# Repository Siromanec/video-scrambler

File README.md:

# video-scrambler
This repository is for "Development of a Composite Baseband Video Signal (CVBS) scrambler" thesis.

## Description

This project contains:
 - Verilog HDL implementation (Quartus Prime 23.1std project) 
 - simulation setup (Modelsim Starter Edition 2021.1 project)
 - jupyter notebooks for visualization and validation of the algorithms
 - KiCAD 9.0 PCB designs for ADV7393 video encoder and TVP5147M1 video decoder

The Verilog implementation is based around line rotation algorithm for scrambling, 
Hash DRBG and SHA256 for number generation. 
It works with BT656 and SMPTE293M digital signal. 
Can synchronise the PRNGs even when the signal is lost. 
The scrambling pattern is different for each frame.
The number of frames before the pattern repeats is 2^32.
The delay is ~ 10^-8 s

The PCB design has the following features:
 - supplied with \> 5V
 - has 4 layers
 - separated power plains
 - all chips pins were wired to external pins (except chroma pins)
 - equalized paths

## Structure and  use
To open each project you need the corresponding IDE
### Notebooks
#### 1. `notebooks/config_creation`

It contains scripts for generating 256-bit seeds and putting them into `.mif` files for configuring the scrambler.

Generates complementary config files for the scrambler and descramber,
#### 2. `notebooks/functional_validation`
It was used to rewrite high-level python implementation
into verilog-friendly algorithm
#### 3. `notebooks/mp_to_bt656`

It contains a notebook used for converting `.mp4` video to `.bin` file compliant with bt656.

Additionally, it is used for visualization the scrambled and descrambled videos and contains the entropy calculations

Also, it has two videos: `aperol.mp4` and `church.mp4`. 
For simulation the user must convert the videos to
`aperol_f84.bin` and `church_f218.bin` and put them into

`FPGA/core/simulation/modelsim/data` or `FPGA/core/simulation/questa/data`

#### 4. `notebooks/randomness_validation`
It was used to validate that the generated random numbers are random
#### 5. `notebooks/resource_usage`
It was used to produce plots of resource usage as compiled by Quartus

### Verilog HDL implementation

`scrambler_mm` is the top module

`FPGA/core` contains the quartus project

`FPGA/core/src` contains rtl and tb code

`FPGA/core/include` contains rtl written by other developers

### Simulation setup

`FPGA/core/simulation/modelsim` contains the modelsim project

To provide the data for the simulation 
you must put it into `FPGA/core/simulation/modelsim/data`.
currently the simulations accepts only two types of files: files generated from `aperol_f84.bin` or `church_f218.bin`.
if you want to change it, you must modify the testbench with names of your files.
Once they are in there, open the project with `modelsim`, goto `project`, see a `sim` folder and in there run
`de/scrambler_mm_sim`. Run the scrambler first, and then the descrambler.
The results will be in `FPGA/core/simulation/modelsim/data` folder.

`FPGA/core/simulation/questa` is generated by quartus for RTL and Gate Level simulations. 
It was only used for GLS of scrambler_mm, because quartus has a bad interface for simulation, 
when the top module changes frequently.

When doing the GLS the user MUST CHANGE THE MIF FILE (for the corresponding functionality) 
AND UPDATE THE MIF FILE (in quartus) OR RECOMPILE when switching 
between scrambling (scrambler_mm_gls_tb) 
and descrambling(descrambler_mm_gls_tb) simulations. 
This is because in gate level simulation the mif file is compiled into the tested module.

### PCB
`PCB/ADV7393BCPZ_encoder` contains the KiCAD project with the corresponding chip

`PCB/TVP5147M1_decoder` contains the KiCAD project with the corresponding chip 
AND the TVP5147M1_decoder and ADV7393BCPZ_encoder on the same PCB

### Results
It contains scrambled and descrambled videos

scrambled

descrambled

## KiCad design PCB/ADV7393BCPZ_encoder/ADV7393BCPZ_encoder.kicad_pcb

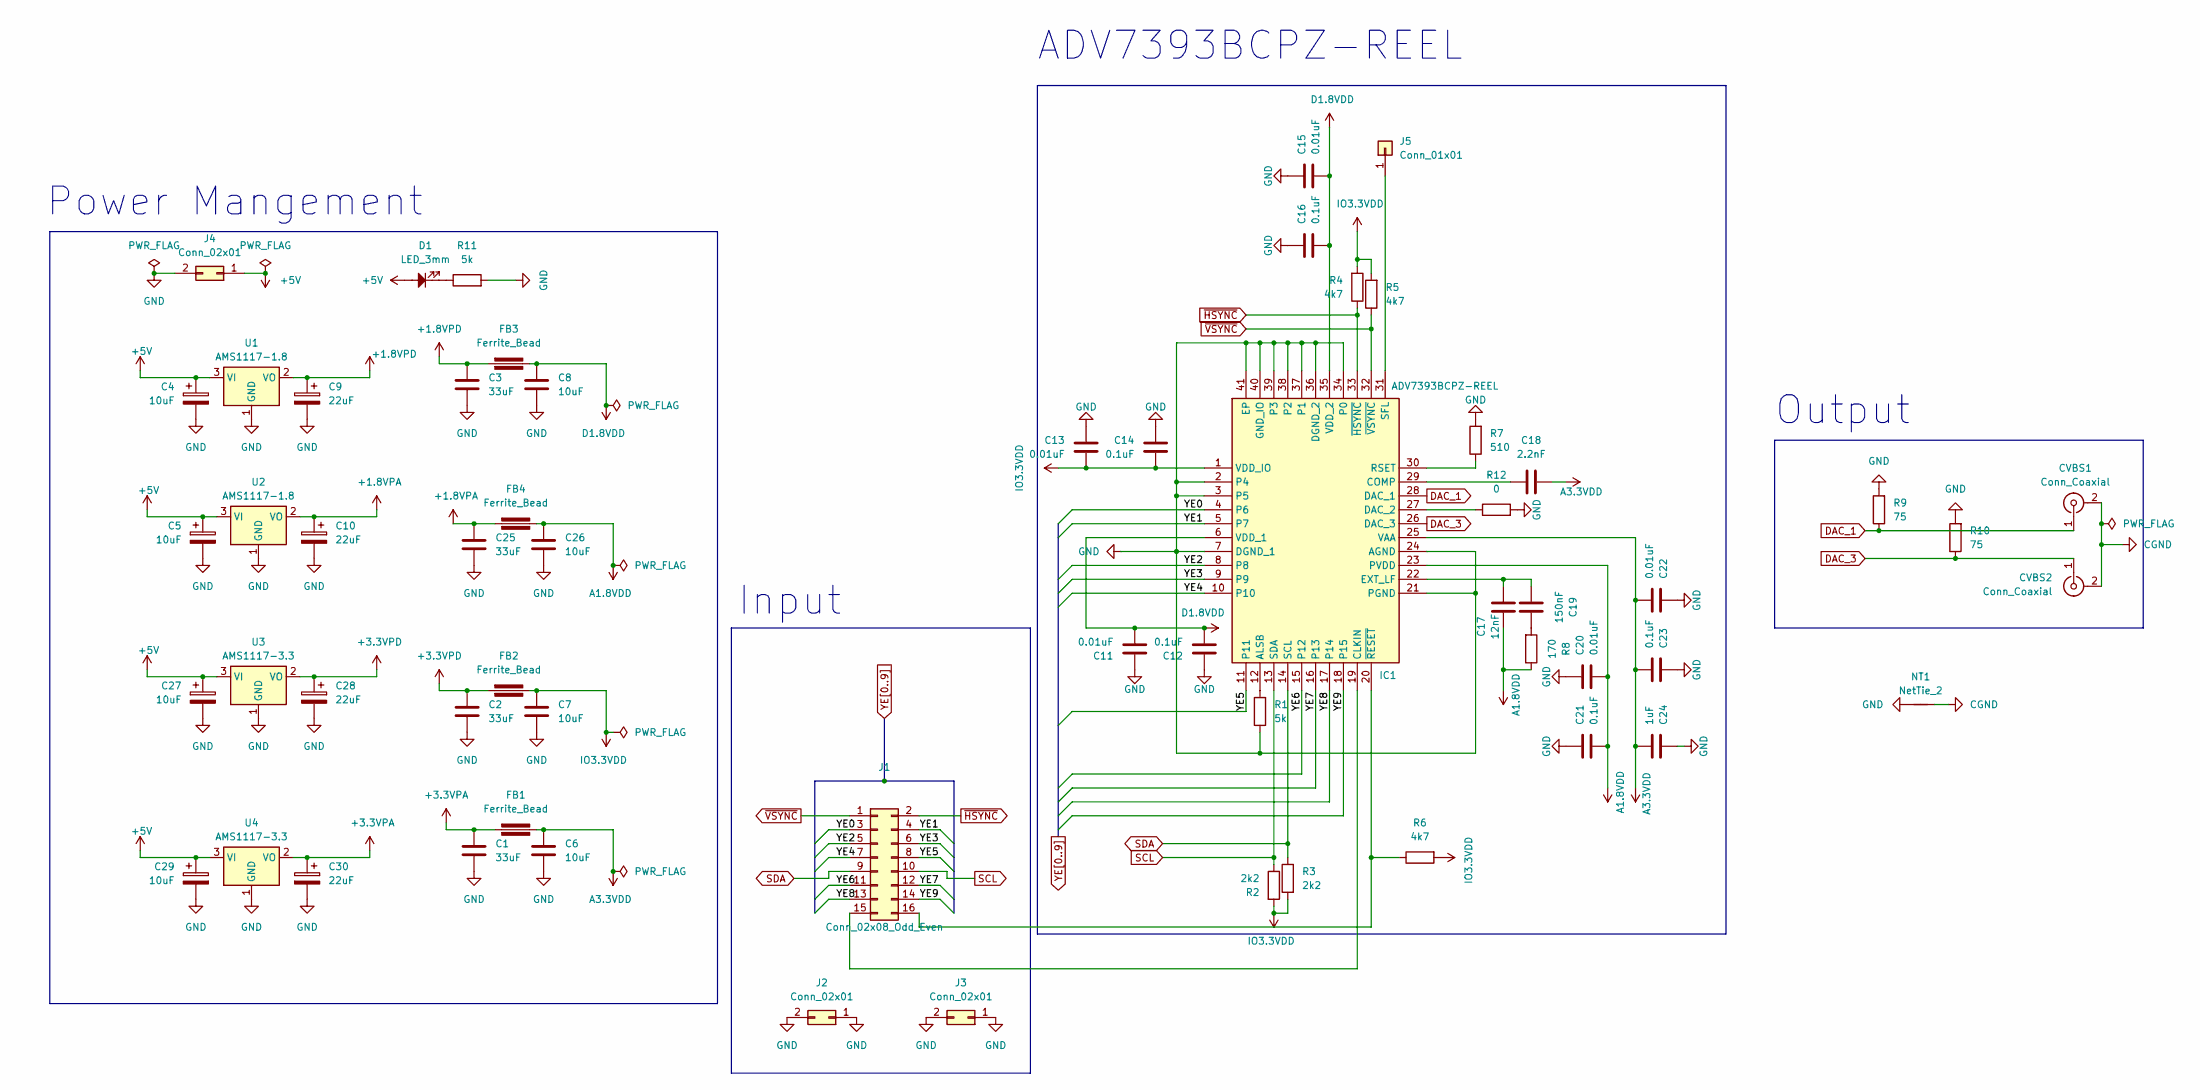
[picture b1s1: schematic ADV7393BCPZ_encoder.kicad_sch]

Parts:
C1, C2, C3, C25: 33uF; CP_EIA-3528-15_AVX-H_Pad1.50x2.35mm_HandSolder
C4, C5, C27, C29: 10uF; CP_Elec_4x5.7
C6, C7, C8, C26: 10uF; CP_EIA-3216-18_Kemet-A_Pad1.58x1.35mm_HandSolder
C9, C10, C28, C30: 22uF; CP_Elec_5x5.7
C11, C13, C15, C20, C22: 0.01uF; C_0603_1608Metric_Pad1.08x0.95mm_HandSolder
C12, C14, C16, C21, C23: 0.1uF; C_0603_1608Metric_Pad1.08x0.95mm_HandSolder
C17: 12nF; C_0603_1608Metric_Pad1.08x0.95mm_HandSolder
C18: 2.2nF; C_0603_1608Metric_Pad1.08x0.95mm_HandSolder
C19: 150nF; C_0603_1608Metric_Pad1.08x0.95mm_HandSolder
C24: 1uF; CP_EIA-3216-18_Kemet-A_Pad1.58x1.35mm_HandSolder
CVBS1, CVBS2: Conn_Coaxial; CC-132-B1
D1: LED_3mm; LED_D3.0mm
FB1, FB2, FB3, FB4: Ferrite_Bead; Ferrite_L6.0mm_D3.5mm_P10.16mm
IC1: ADV7393BCPZ-REEL; LFCSP-40-1EP_6x6mm_P0.5mm_EP3.9x3.9mm_ThermalVias; Manufacturer_Part_Number ADV7393BCPZ-REEL; Mouser Part Number 584-ADV7393BCPZ-R
J1: Conn_02x08_Odd_Even; PinHeader_2x08_P2.54mm_Vertical
J2, J3, J4: Conn_02x01; PinHeader_2x01_P2.54mm_Vertical
J5: Conn_01x01; PinHeader_1x01_P2.54mm_Vertical
NT1: NetTie_2; NetTie-2_THT_Pad1.0mm
R1: 5k; R_0603_1608Metric_Pad0.98x0.95mm_HandSolder
R2, R3: 2k2; R_0603_1608Metric_Pad0.98x0.95mm_HandSolder
R4, R5, R6: 4k7; R_0603_1608Metric_Pad0.98x0.95mm_HandSolder
R7: 510; R_0603_1608Metric_Pad0.98x0.95mm_HandSolder
R8: 170; R_0603_1608Metric_Pad0.98x0.95mm_HandSolder
R9, R10: 75; R_0603_1608Metric_Pad0.98x0.95mm_HandSolder
R11: 5k; R_0603_1608Metric_Pad1.05x0.95mm_HandSolder
R12: 0; R_0603_1608Metric_Pad0.98x0.95mm_HandSolder
U1, U2: AMS1117-1.8; SOT-223-3_TabPin2
U3, U4: AMS1117-3.3; SOT-223-3_TabPin2

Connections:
+1.8VPA: C10.1, C25.1, FB4.1, U2.2 (VO)
+1.8VPD: C3.1, C9.1, FB3.1, U1.2 (VO)
+3.3VPA: C1.1, C30.1, FB1.1, U4.2 (VO)
+3.3VPD: C2.1, C28.1, FB2.1, U3.2 (VO)
+5V: C4.1, C5.1, C27.1, C29.1, D1.2, J4.1, U1.3 (VI), U2.3 (VI), U3.3 (VI), U4.3 (VI)
A1.8VDD: C17.2, C20.1, C21.2, C26.1, FB4.2, IC1.23 (PVDD), R8.1
A3.3VDD: C6.1, C18.2, C22.1, C23.2, C24.1, FB1.2, IC1.25 (VAA)
CGND: CVBS1.2 (Ext), CVBS2.2 (Ext), NT1.2
D1.8VDD: C8.1, C11.1, C12.2, C15.1, C16.2, FB3.2, IC1.6 (VDD_1), IC1.35 (VDD_2)
DAC_1: CVBS1.1 (In), IC1.28 (DAC_1), R9.1
DAC_3: CVBS2.1 (In), IC1.26 (DAC_3), R10.1
GND: C1.2, C2.2, C3.2, C4.2, C5.2, C6.2, C7.2, C8.2, C9.2, C10.2, C11.2, C12.1, C13.2, C14.1, C15.2, C16.1, C20.2, C21.1, C22.2, C23.1, C24.2, C25.2, C26.2, C27.2, C28.2, C29.2, C30.2, IC1.2 (P4), IC1.3 (P5), IC1.7 (DGND_1), IC1.21 (PGND), IC1.24 (AGND), IC1.34 (P0), IC1.36 (DGND_2), IC1.37 (P1), IC1.38 (P2), IC1.39 (P3), IC1.40 (GND_IO), IC1.41 (EP), J2.1, J2.2, J3.1, J3.2, J4.2, NT1.1, R1.1, R7.2, R9.2, R10.2, R11.2, R12.2, U1.1 (GND), U2.1 (GND), U3.1 (GND), U4.1 (GND)
IO3.3VDD: C7.1, C13.1, C14.2, FB2.2, IC1.1 (VDD_IO), R2.2, R3.2, R4.2, R5.2, R6.2
unnamed: C19.2, R8.2
unnamed: D1.1, R11.1
unnamed: IC1.12 (ALSB), R1.2
unnamed: IC1.19 (CLKIN), J1.15
unnamed: C18.1, IC1.29 (COMP)
unnamed: IC1.27 (DAC_2), R12.1
unnamed: C17.1, C19.1, IC1.22 (EXT_LF)
unnamed: IC1.30 (RSET), R7.1
unnamed: IC1.31 (SFL), J5.1
unnamed: IC1.20 (~RESET), J1.16, R6.1
SCL: IC1.13 (SDA), J1.10, R2.1
SDA: IC1.14 (SCL), J1.9, R3.1
YE0: IC1.4 (P6), J1.3
YE1: IC1.5 (P7), J1.4
YE2: IC1.8, J1.5
YE3: IC1.9, J1.6
YE4: IC1.10, J1.7
YE5: IC1.11, J1.8
YE6: IC1.15 (P12), J1.11
YE7: IC1.16 (P13), J1.12
YE8: IC1.17 (P14), J1.13
YE9: IC1.18 (P15), J1.14
~HSYNC: IC1.33 (~HSYNC), J1.2, R4.1
~VSYNC: IC1.32 (~VSYNC), J1.1, R5.1

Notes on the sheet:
ADV7393BCPZ-REEL
Output
Power Mangement
Input

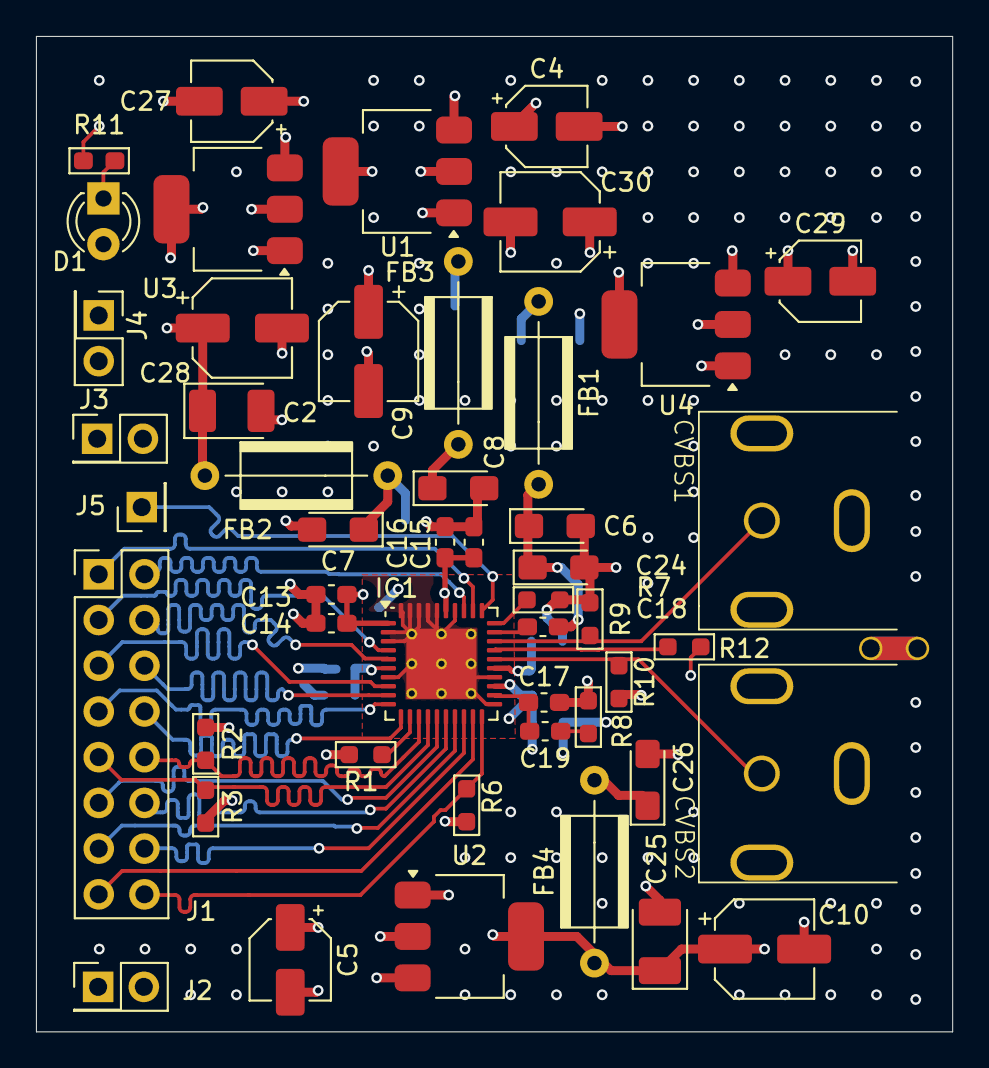
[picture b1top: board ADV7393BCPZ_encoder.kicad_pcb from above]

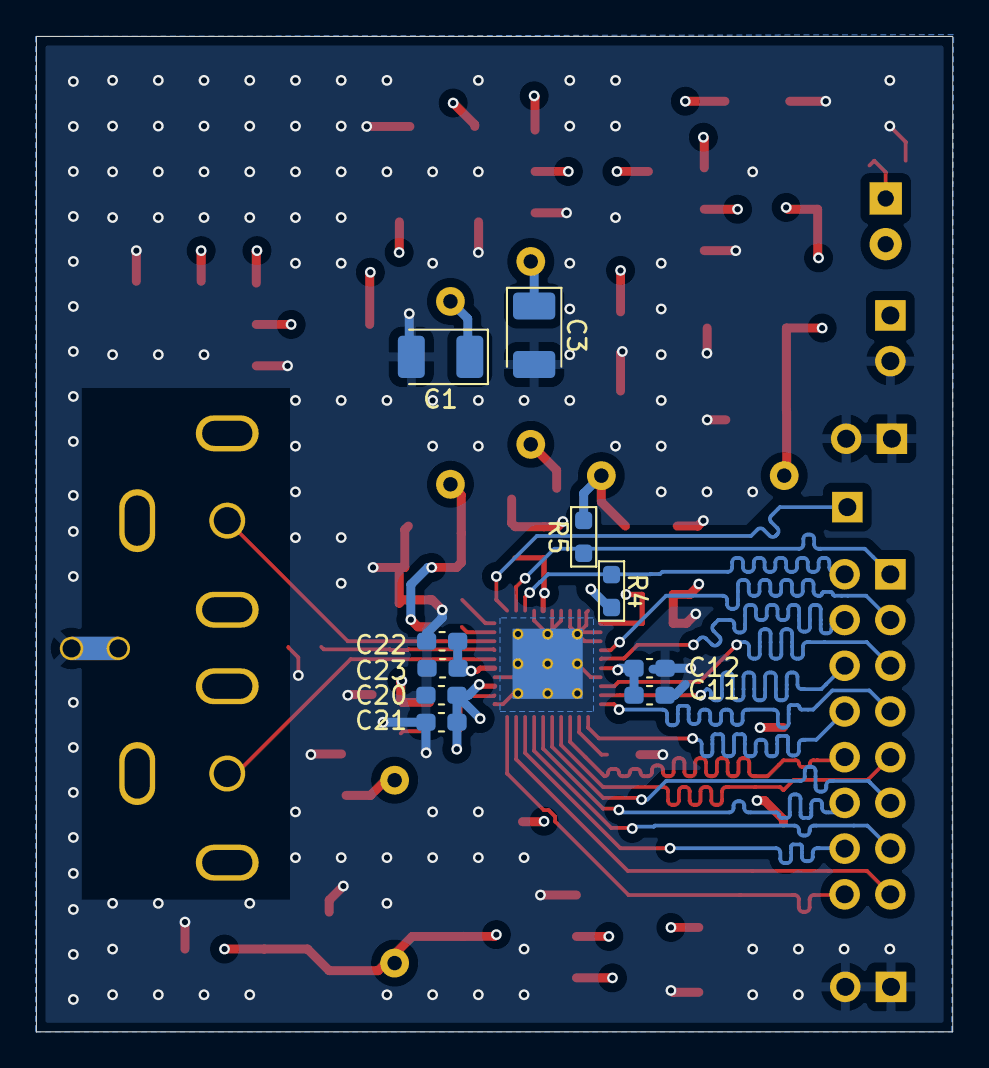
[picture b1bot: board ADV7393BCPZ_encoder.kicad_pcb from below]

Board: 4 copper layers, 50.9 x 55.3 mm, 60 parts (10 on the bottom side), 37 nets.

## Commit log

2025-03-08 initial project commit
2025-03-09 added basic rom memory configuration
2025-03-09 cleanup
2025-03-09 finished i2c
2025-03-09 i2c changes
2025-03-09 stole someone's i2c
2025-03-09 added cfg reader for a single divice
2025-03-10 assembled init module
2025-03-15 basic pcb
2025-03-17 decoder pcb almost done
2025-03-24 added basic hash_drbg
2025-03-24 fixed main bugs in hash_drbg
2025-03-26 hash_drbg is working, trying to add double_hash_drbg
2025-03-26 got double hash drbg working in master mode
2025-03-26 randomness test
2025-03-29 sequence generator works as intended now
2025-03-30 sequence detector is working
2025-03-30 structure refactoring
2025-03-31 updated peak levels and wrote the first half of mp4 to bt656 converter (data ordered correctly,but requires transformation to binary)
2025-04-02 added transformation to binary and back
2025-04-02 added conversion from bin to video that can be played in jupyter
2025-04-02 added functional scrambler implementation in jupyter
2025-04-02 sync parser works
2025-04-03 cut position interpolator works
2025-04-05 line rotation scrambling works and does not take up now 20000 registers. Descrambling needs testing
2025-04-06 descrambling works
2025-04-06 added data valid flag
2025-04-06 made it so that the cut position won't change until the end of hsync. It should make the line rotator more decoupled from the outside
2025-04-08 updated hash_drbg to have a busy signal; changed blocking assignments to non-blocking;
2025-04-08 added posedge to pulse back;
2025-04-08 wrote and tested hash drbg consumer; needs randomness test just to be sure; works independently of sample count in a line and does not depend on number of lines;
2025-04-08 added lock for writing and evaluated randomness
2025-04-08 removed a bug where the consumer was begging for the next bits during hsync
2025-04-09 video format bugfixes
2025-04-09 scrambler and descrambler consumed drbg at different moments =)
2025-04-09 removed 2nd buffer and in consumer and fixed a bug where write_done would be high too soon
2025-04-09 restructured consumer logic and my drbg is working for line rotation
2025-04-09 hacked line rotation scrambler
2025-04-10 sequence_generator_switch now works
2025-04-11 name refactor double_hash_drbg -> master_hash_slave_hash_drbg hash_drbg_consumer -> drbg_consumer
2025-04-11 ignor black boxes
2025-04-11 sequence detector works on bt656 stream
2025-04-11 notebook location refactor
2025-04-11 wrote drbg_synchronisator
2025-04-11 modelsim refactor
2025-04-11 found working formatter
2025-04-11 removed manual init for drbg, because it was annoying and useless
2025-04-11 updated data paths
2025-04-12 drbg synch works.
2025-04-12 Drbg can give the result 2x sooner
2025-04-12 preparation for writing the final scrambler
2025-04-12 added faster file reading and fixed a bug that did not scramble the last line in the video
2025-04-14 final scrambler assembled. line rotator in scrambling mode needed to delay the V signal. Modelsim did some magic 0-tick pulses that broke everything
2025-04-14 fixed off-by-one error in switch and logical error in synchronisator
2025-04-14 final scrambler and descrambler assembled and they work flawlessly. Descrambler can catch up to the scrambled video at any point. Thinking whether I should leave conditional compilation for scrambler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
2025-04-14 added documentation
2025-04-15 added memory initialization interface for the scrambler, reduced the number of LUTs used by the drbg, added design files for the video decoder, added scripts for generating keys and uploading them to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
2025-04-16 ran experiments
2025-04-16 reduced resource usage of drbg by replacing my master-slave algorithm with original Hash DRBG
2025-04-22 removed extra states and tristate busses in hash drbg. saving before a big refactor that will break everything. in particular the long master-slave name and the decoder thingy that stuck from the beg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
2025-04-22 replaced master_hash_slave_hash_drbg with hash_drbg_sha256
2025-04-22 renamed the project
2025-04-24 renamed synchronizer and rom_scrambler. Fixed a bug where sequence magic number was not matched correctly. Added source file selection from cli (+define+) to scrambler_tb
2025-04-24 better frame and entropy visualizations
2025-04-24 testing out various scrambling algorithms and breaking them
2025-04-24 visualizing resource usage
2025-04-24 added videos to git lfs
2025-04-24 moved and added resource usage
2025-04-24 changed modelsim absolute paths to relative
2025-04-24 inited git lfs
2025-04-24 git attribute change
2025-04-24 update gitignore
2025-04-24 add files to lfs
2025-04-25 changed sync detection so that hsync signal is active when eav starts (not ends)
2025-04-26 added testbenches and configs for scrambler_mm
2025-04-30 added chages relating GLS, so that it would work and debug outputs for the scrambler
2025-05-01 added readme and notebook cleanup
2025-05-01 removed debug mode
